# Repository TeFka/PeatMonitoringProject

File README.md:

# University group project
# Peat monitoring device
### This is the repository for used for storage of all relevant resources used for the university group project.<br>
### The project involved development of a device that would be placed in a peat and provides measuremetns about the peat state.</br>
### Measurements include:
* Surface elevation - shows how much peat surface changed water in it.</br>
* Water pressure - shows the pressure created by the peat water table.</br>
* Temperature - shows temperature of surroundings around the device.</br>
* Operate for at least 6 months unsupervised and store all data.</br>
### A poster was created for the device:</br>
</br>
### The respository was created and managed by Danielius Zurlys. Project work done by Danielius Zurlys:<br>
* All embedded software<br>
* Hardware and mechanical designs for pressure sensor<br>
* Hardware and mechanical designs for temperature sensor<br>
### Work done by other group members:<br>
* Oliver Davies - Developed PCB for STM32<br>
* Chuan Loo - Developed PCB for battery control<br>
* Sever Dragomir - Design for main case and elevantion sensor.<br>
* James Bodenham - RF communication hardware choice and logic<br>

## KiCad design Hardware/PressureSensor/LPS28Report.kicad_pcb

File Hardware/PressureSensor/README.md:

# Pressure sensor PCB
Developed PCB to host pressure sensor. The used pressure sensor is LPS28DFW (.pdf datasheet file provded).
The sensor is very small and the PCB is meant to enable connection between sensor and standart connections.

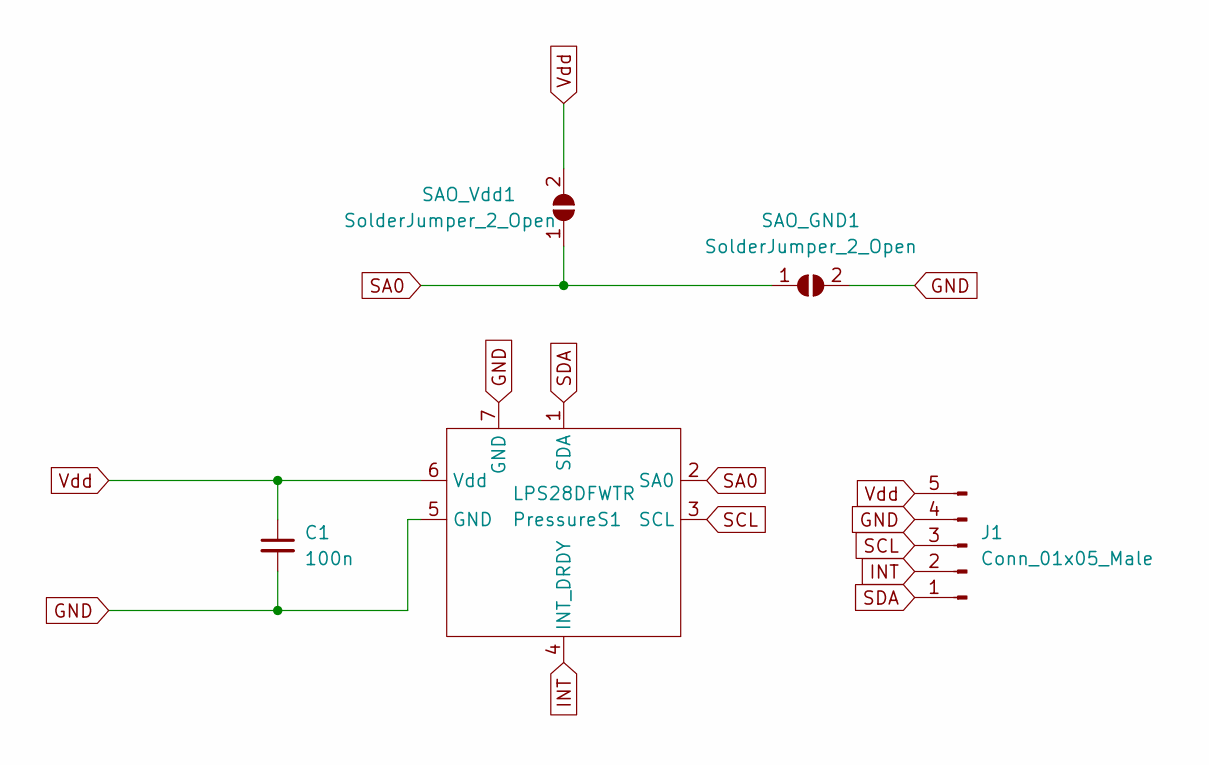
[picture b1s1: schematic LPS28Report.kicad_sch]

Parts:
C1: 100n; C_0603_1608Metric_Pad1.08x0.95mm_HandSolder
J1: Conn_01x05_Male; PinHeader_1x05_P1.00mm_Vertical_SMD_Pin1Left
PressureS1: LPS28DFWTR
SAO_GND1: SolderJumper_2_Open; SolderJumper-2_P1.3mm_Open_Pad1.0x1.5mm
SAO_Vdd1: SolderJumper_2_Open; SolderJumper-2_P1.3mm_Open_Pad1.0x1.5mm

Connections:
GND: C1.2, J1.4, PressureS1.5 (GND), PressureS1.7 (GND), SAO_GND1.2 (B)
INT: J1.2, PressureS1.4 (INT_DRDY)
SA0: PressureS1.2 (SA0), SAO_GND1.1 (A), SAO_Vdd1.1 (A)
SCL: J1.3, PressureS1.3 (SCL)
SDA: J1.1, PressureS1.1 (SDA)
Vdd: C1.1, J1.5, PressureS1.6 (Vdd), SAO_Vdd1.2 (B)

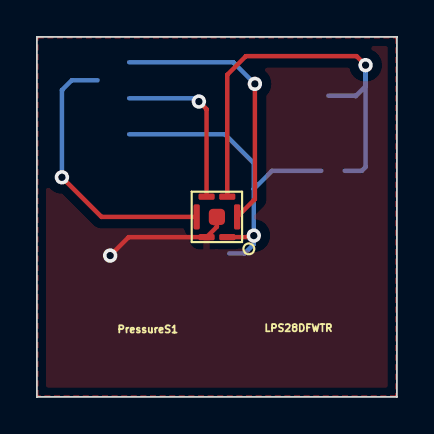
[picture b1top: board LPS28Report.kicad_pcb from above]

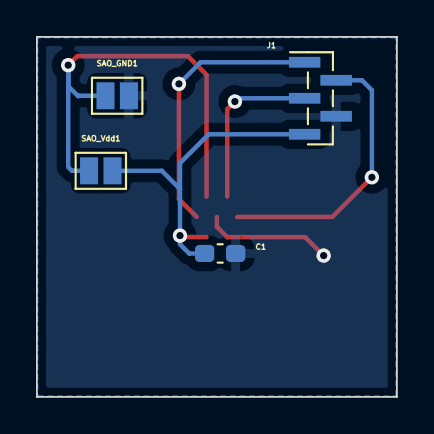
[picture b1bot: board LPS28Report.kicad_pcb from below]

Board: 2 copper layers, 20.0 x 20.0 mm, 5 parts (4 on the bottom side), 6 nets.

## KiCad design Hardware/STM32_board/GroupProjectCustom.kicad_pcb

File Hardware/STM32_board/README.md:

# STM32 chip PCB</br>
Designed by Oliver Davies</br>
The main PCB for STM32 chip. Provides SPI, I2C, UART and analogue connections that allow communicaton with all relevant components. Connection to the battery is also availalbe to provide power.</br>

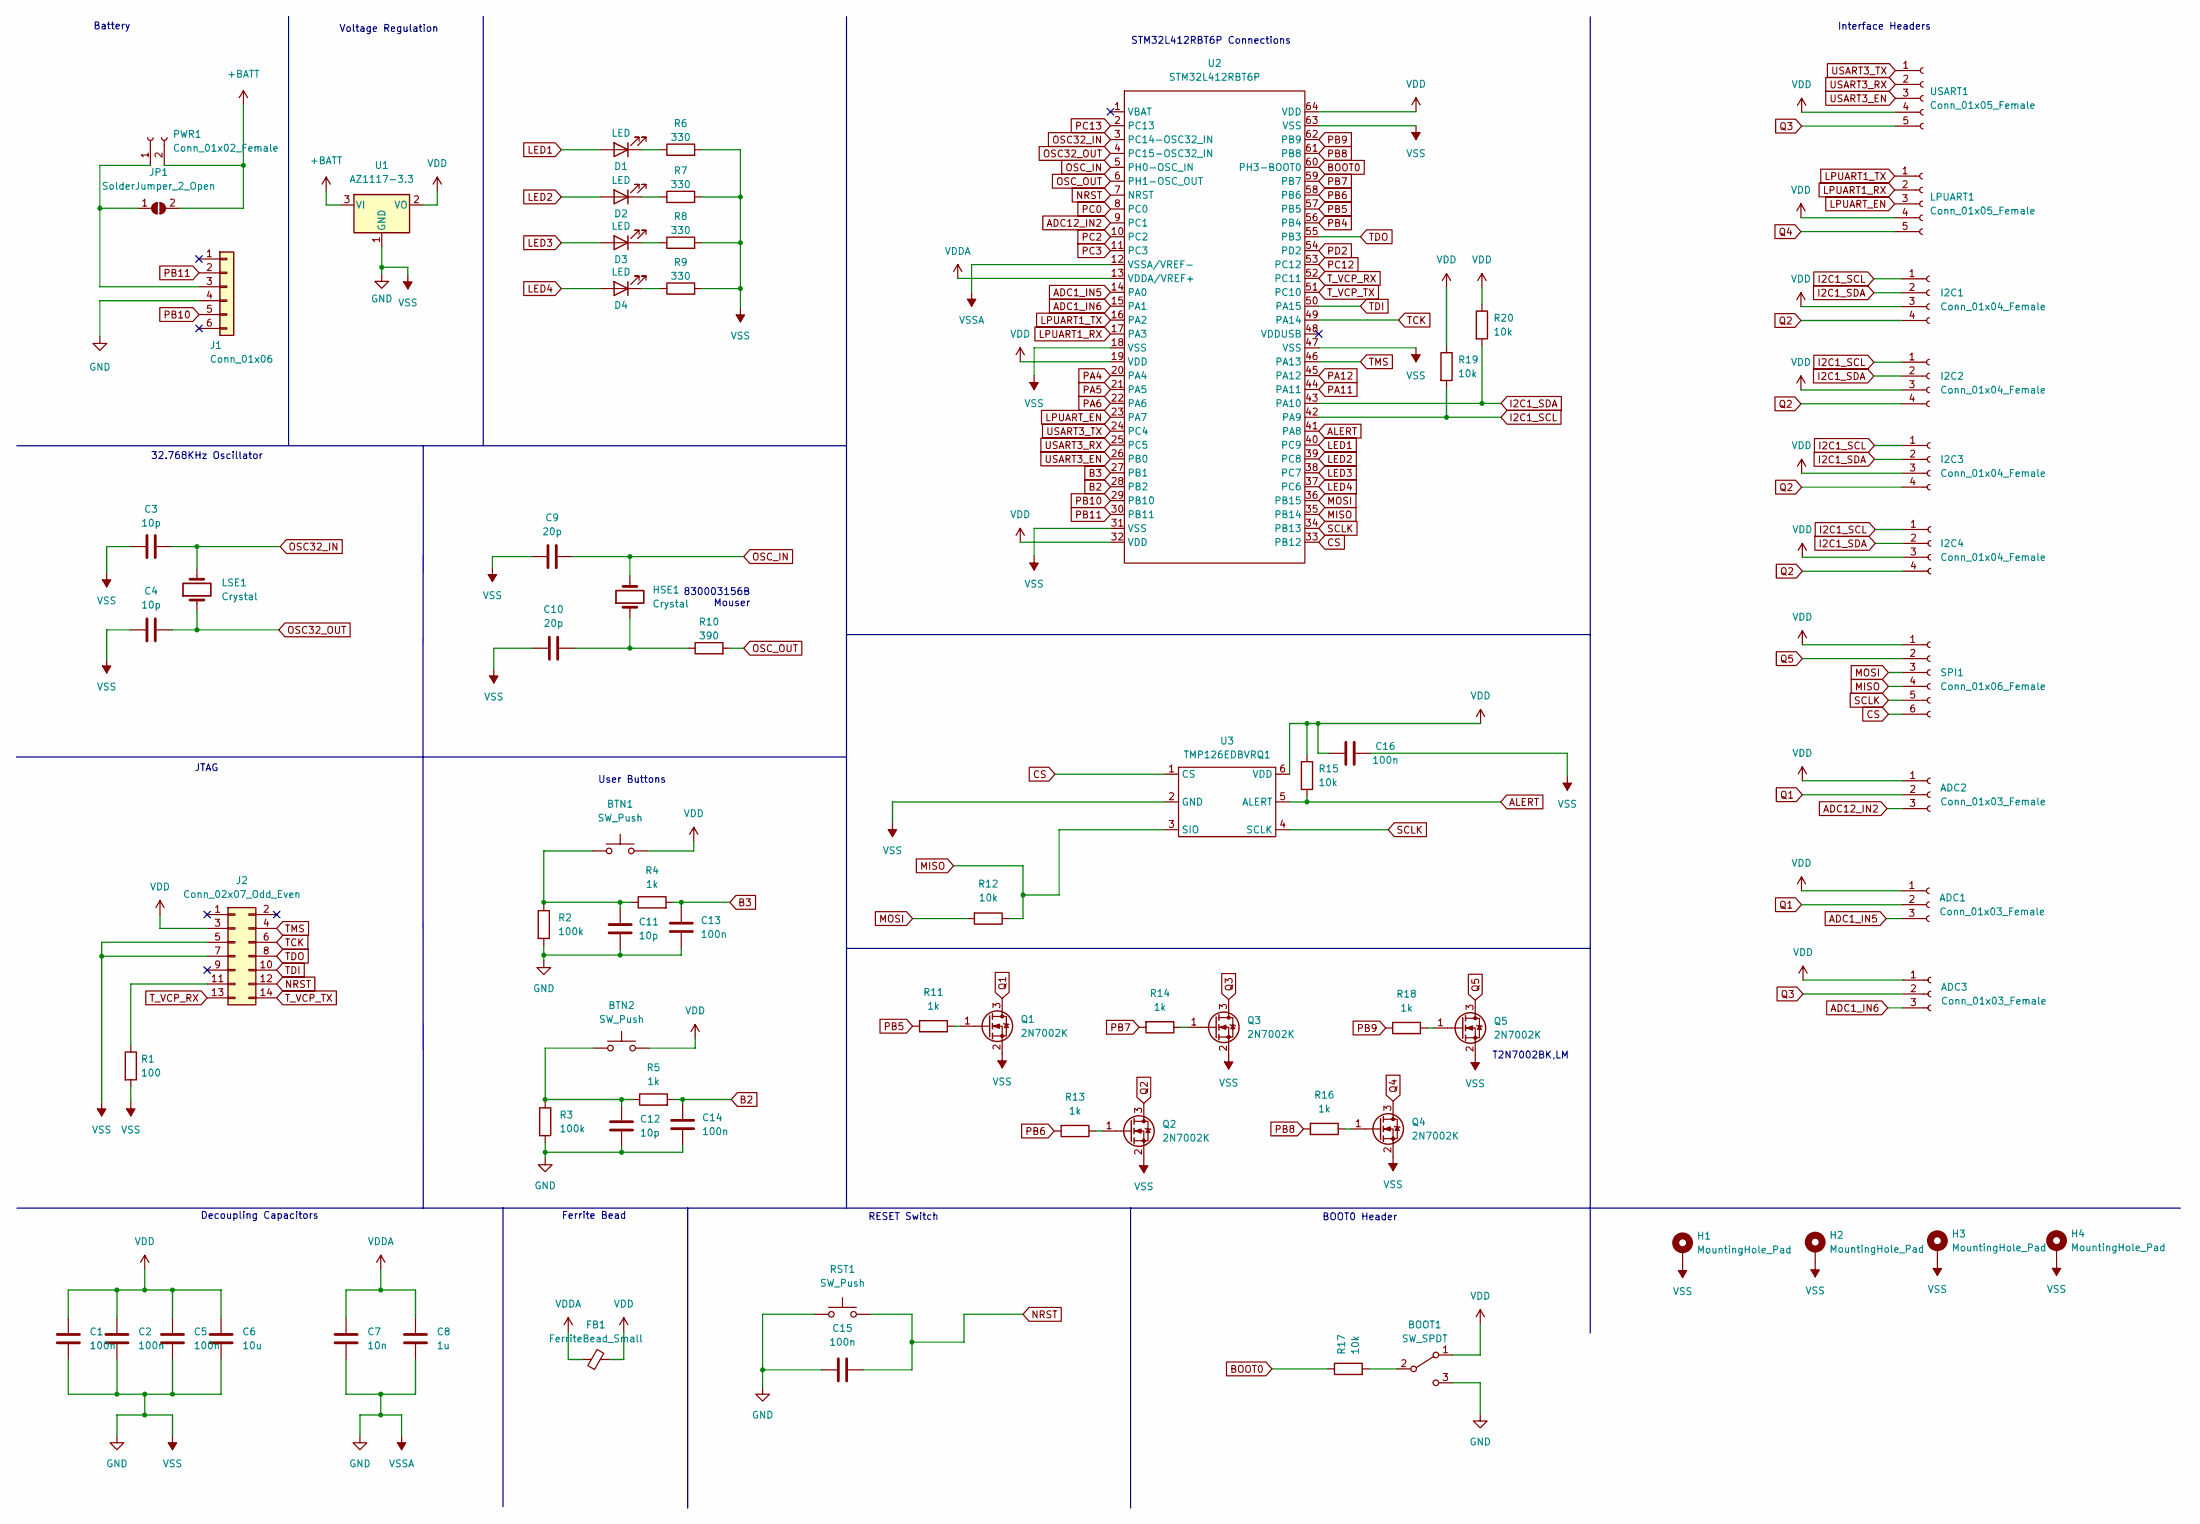
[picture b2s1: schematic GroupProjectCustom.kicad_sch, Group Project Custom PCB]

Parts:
ADC1, ADC2, ADC3: Conn_01x03_Female; PinHeader_1x03_P2.54mm_Vertical
BOOT1: SW_SPDT; PinHeader_1x03_P2.54mm_Vertical
BTN1, BTN2: SW_Push; SW_Push_1P1T_NO_Vertical_Wuerth_434133025816
C1, C2, C5, C13, C14, C15, C16: 100n; C_0603_1608Metric_Pad1.08x0.95mm_HandSolder
C3, C4, C11, C12: 10p; C_0603_1608Metric_Pad1.08x0.95mm_HandSolder
C6: 10u; C_0603_1608Metric_Pad1.08x0.95mm_HandSolder
C7: 10n; C_0603_1608Metric_Pad1.08x0.95mm_HandSolder
C8: 1u; C_0603_1608Metric_Pad1.08x0.95mm_HandSolder
C9, C10: 20p; C_0603_1608Metric_Pad1.08x0.95mm_HandSolder
D1, D2, D3, D4: LED; LED_0603_1608Metric_Pad1.05x0.95mm_HandSolder
FB1: FerriteBead_Small; R_0603_1608Metric_Pad0.98x0.95mm_HandSolder
H1, H2, H3, H4: MountingHole_Pad; MountingHole_2.2mm_M2_Pad_Via
HSE1: Crystal; Crystal_HC49-4H_Vertical
I2C1, I2C2, I2C3, I2C4: Conn_01x04_Female; PinHeader_1x04_P2.54mm_Vertical
J1: Conn_01x06; PinHeader_1x06_P2.54mm_Vertical
J2: Conn_02x07_Odd_Even; PinHeader_2x07_P1.27mm_Vertical_SMD
JP1: SolderJumper_2_Open; SolderJumper-2_P1.3mm_Open_TrianglePad1.0x1.5mm
LPUART1: Conn_01x05_Female; PinHeader_1x05_P2.54mm_Vertical
LSE1: Crystal; Crystal_SMD_MicroCrystal_CC7V-T1A-2Pin_3.2x1.5mm_HandSolder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
PWR1: Conn_01x02_Female; PinHeader_1x02_P2.54mm_Vertical
Q1, Q2, Q3, Q4, Q5: 2N7002K; SOT-23
R1: 100; R_0603_1608Metric
R2, R3: 100k; R_0603_1608Metric
R4, R5, R11, R13, R14, R16, R18: 1k; R_0603_1608Metric
R6, R7, R8, R9: 330; R_0603_1608Metric
R10: 390; R_0603_1608Metric
R12, R15, R17, R19, R20: 10k; R_0603_1608Metric
RST1: SW_Push; SW_Push_1P1T_NO_Vertical_Wuerth_434133025816
SPI1: Conn_01x06_Female; PinHeader_1x06_P2.54mm_Vertical
U1: AZ1117-3.3; SOT-223-3_TabPin2
U2: STM32L412RBT6P; STM32L412RBT6P_Foot
U3: TMP126EDBVRQ1; SOT-23-6_Handsoldering
USART1: Conn_01x05_Female; PinHeader_1x05_P2.54mm_Vertical

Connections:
+BATT: JP1.2 (B), PWR1.2, U1.3 (VI)
ADC1_IN5: ADC1.3, U2.14 (PA0)
ADC1_IN6: ADC3.3, U2.15 (PA1)
ADC12_IN2: ADC2.3, U2.9 (PC1)
ALERT: R15.2, U2.41 (PA8), U3.5 (ALERT)
B2: C14.1, R5.2, U2.28 (PB2)
B3: C13.1, R4.2, U2.27 (PB1)
BOOT0: R17.1, U2.60 (PH3-BOOT0)
CS: SPI1.6, U2.33 (PB12), U3.1 (CS)
GND: BOOT1.3 (C), C1.2, C2.2, C3.1, C4.1, C5.2, C6.2, C7.2, C8.2, C9.1, C10.1, C11.1, C12.1, C13.2, C14.2, C15.1, C16.2, H1.1, H2.1, H3.1, H4.1, J1.4, J2.5, J2.7, Q1.2 (S), Q2.2 (S), Q3.2 (S), Q4.2 (S), Q5.2 (S), R1.2, R2.2, R3.2, R6.2, R7.2, R8.2, R9.2, RST1.1, U1.1 (GND), U2.12 (VSSA/VREF-), U2.18 (VSS), U2.31 (VSS), U2.47 (VSS), U2.63 (VSS), U3.2 (GND)
I2C1_SCL: I2C1.1, I2C2.1, I2C3.1, I2C4.1, R19.2, U2.42 (PA9)
I2C1_SDA: I2C1.2, I2C2.2, I2C3.2, I2C4.2, R20.2, U2.43 (PA10)
LED1: D1.2 (A), U2.40 (PC9)
LED2: D2.2 (A), U2.39 (PC8)
LED3: D3.2 (A), U2.38 (PC7)
LED4: D4.2 (A), U2.37 (PC6)
LPUART1_RX: LPUART1.2, U2.17 (PA3)
LPUART1_TX: LPUART1.1, U2.16 (PA2)
LPUART_EN: LPUART1.3, U2.23 (PA7)
MISO: R12.1, SPI1.4, U2.35 (PB14), U3.3 (SIO)
MOSI: R12.2, SPI1.3, U2.36 (PB15)
NRST: C15.2, J2.12, RST1.2, U2.7 (NRST)
unnamed: BOOT1.2 (B), R17.2
unnamed: BTN1.1, C11.2, R2.1, R4.1
unnamed: BTN2.1, C12.2, R3.1, R5.1
unnamed: C10.2, HSE1.1, R10.1
unnamed: D1.1 (K), R6.1
unnamed: D2.1 (K), R7.1
unnamed: D3.1 (K), R8.1
unnamed: D4.1 (K), R9.1
unnamed: J1.3, JP1.1 (A), PWR1.1
unnamed: J2.11, R1.1
unnamed: Q1.1 (G), R11.1
unnamed: Q2.1 (G), R13.1
unnamed: Q3.1 (G), R14.1
unnamed: Q4.1 (G), R16.1
unnamed: Q5.1 (G), R18.1
OSC32_IN: C3.2, LSE1.2, U2.3 (PC14-OSC32_IN)
OSC32_OUT: C4.2, LSE1.1, U2.4 (PC15-OSC32_IN)
OSC_IN: C9.2, HSE1.2, U2.5 (PH0-OSC_IN)
OSC_OUT: R10.2, U2.6 (PH1-OSC_OUT)
PA4: U2.20 (PA4)
PA5: U2.21 (PA5)
PA6: U2.22 (PA6)
PA11: U2.44 (PA11)
PA12: U2.45 (PA12)
PB4: U2.56 (PB4)
PB5: R11.2, U2.57 (PB5)
PB6: R13.2, U2.58 (PB6)
PB7: R14.2, U2.59 (PB7)
PB8: R16.2, U2.61 (PB8)
PB9: R18.2, U2.62 (PB9)
PB10: J1.5, U2.29 (PB10)
PB11: J1.2, U2.30 (PB11)
PC0: U2.8 (PC0)
PC2: U2.10 (PC2)
PC3: U2.11 (PC3)
PC12: U2.53 (PC12)
PC13: U2.2 (PC13)
PD2: U2.54 (PD2)
Q1: ADC1.2, ADC2.2, Q1.3 (D)
Q2: I2C1.4, I2C2.4, I2C3.4, I2C4.4, Q2.3 (D)
Q3: ADC3.2, Q3.3 (D), USART1.5
Q4: LPUART1.5, Q4.3 (D)
Q5: Q5.3 (D), SPI1.2
SCLK: SPI1.5, U2.34 (PB13), U3.4 (SCLK)
TCK: J2.6, U2.49 (PA14)
TDI: J2.10, U2.50 (PA15)
TDO: J2.8, U2.55 (PB3)
TMS: J2.4, U2.46 (PA13)
T_VCP_RX: J2.13, U2.52 (PC11)
T_VCP_TX: J2.14, U2.51 (PC10)
USART3_EN: U2.26 (PB0), USART1.3
USART3_RX: U2.25 (PC5), USART1.2
USART3_TX: U2.24 (PC4), USART1.1
VDD: ADC1.1, ADC2.1, ADC3.1, BOOT1.1 (A), BTN1.2, BTN2.2, C1.1, C2.1, C5.1, C6.1, C16.1, FB1.2, I2C1.3, I2C2.3, I2C3.3, I2C4.3, J2.3, LPUART1.4, R15.1, R19.1, R20.1, SPI1.1, U1.2 (VO), U2.19 (VDD), U2.32 (VDD), U2.64 (VDD), U3.6 (VDD), USART1.4
VDDA: C7.1, C8.1, FB1.1, U2.13 (VDDA/VREF+)

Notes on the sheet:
RESET Switch
JTAG
BOOT0 Header
Ferrite Bead
User Buttons
STM32L412RBT6P Connections
Interface Headers
Decoupling Capacitors
Voltage Regulation
Battery
32.768KHz Oscillator
830003156B Mouser
T2N7002BK,LM

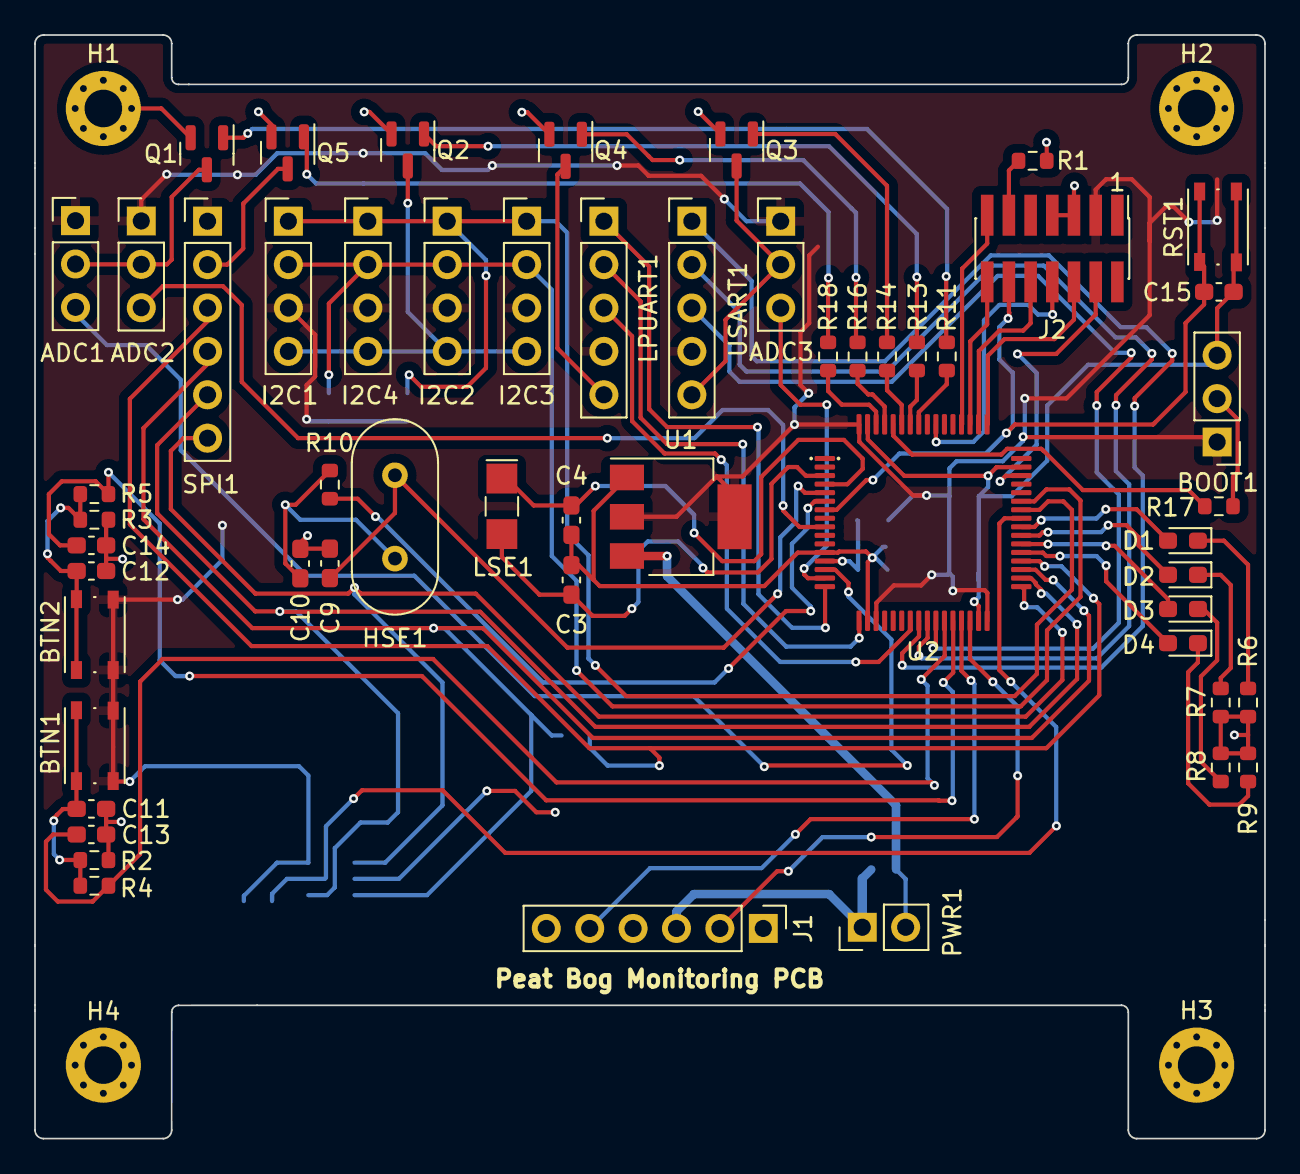
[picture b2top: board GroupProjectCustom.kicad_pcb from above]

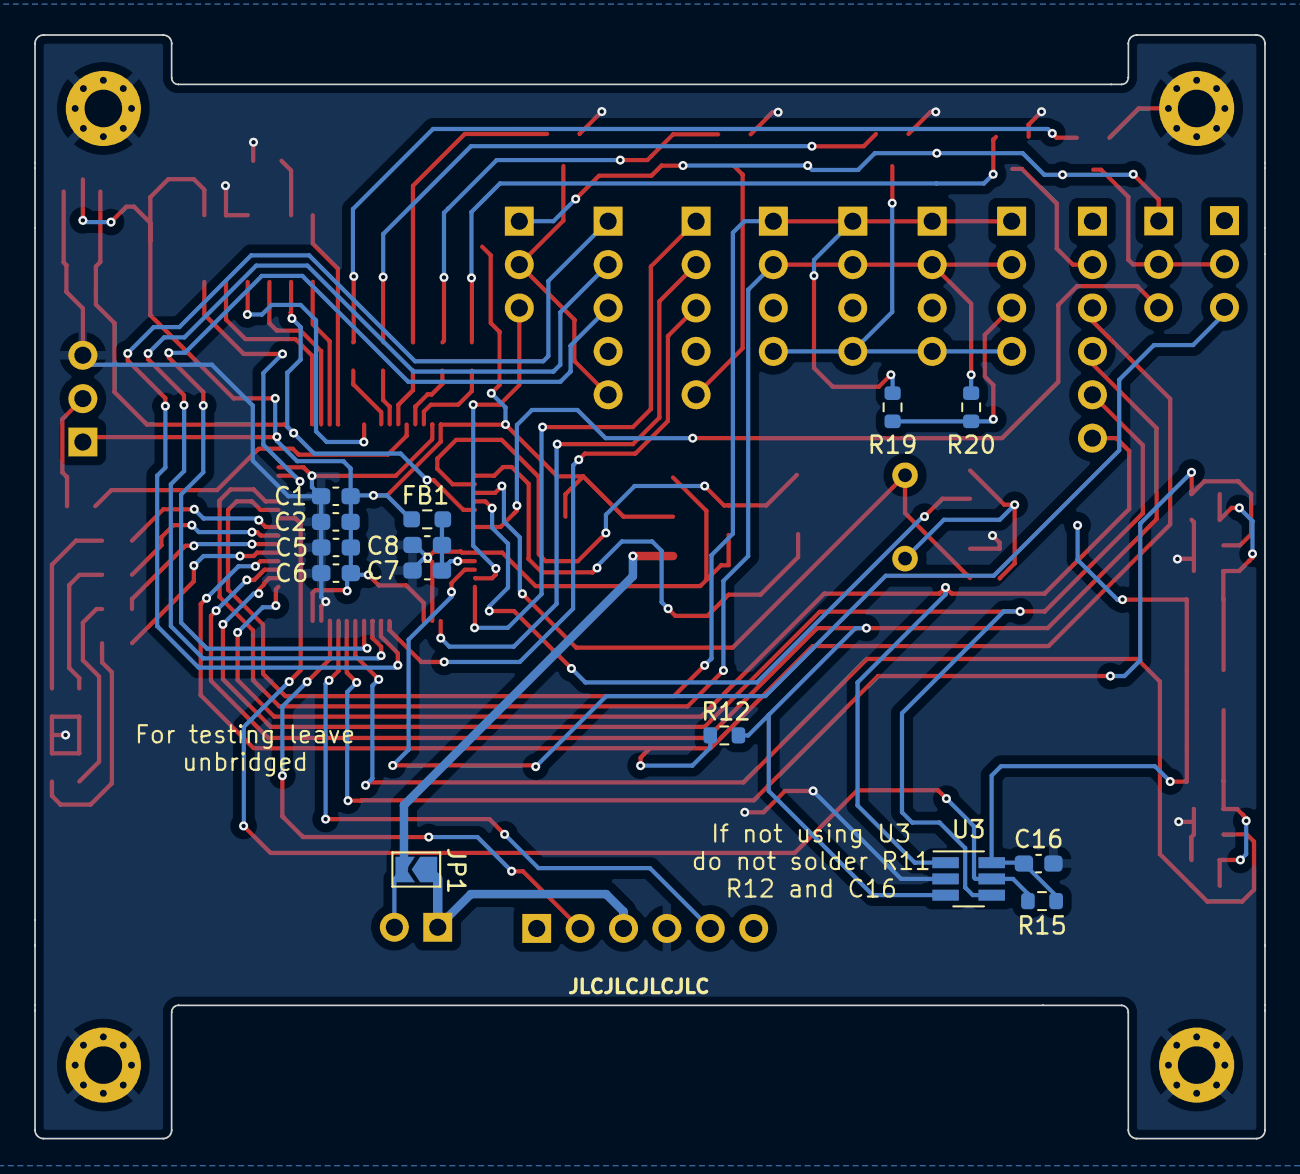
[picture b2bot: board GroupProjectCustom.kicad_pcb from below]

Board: 2 copper layers, 72.0 x 64.6 mm, 73 parts (14 on the bottom side), 65 nets.

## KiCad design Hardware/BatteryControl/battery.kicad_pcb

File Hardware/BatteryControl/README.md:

# Battery management PCB PCB</br>
### Designed by Chuan Loo</br>
### The PCB is meant to allow efficient and safew usage of batteries. Main functions are:</br>
* Reduce battery voltage to safe levels for the PCB.</br
* Use one battery at a time even if two are connected, when one battery is depleted, only then the PCB starts retrieving power from second battery.</br

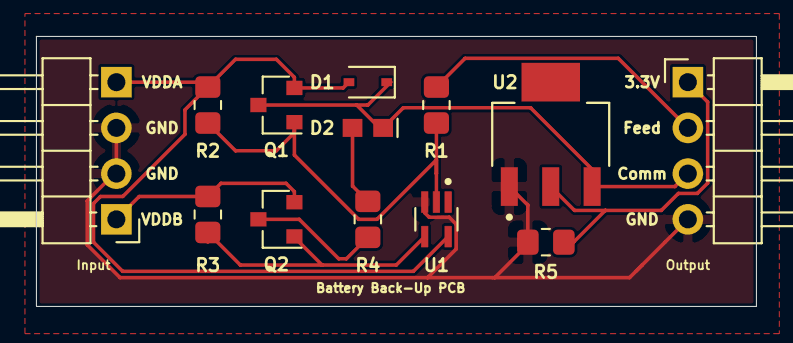
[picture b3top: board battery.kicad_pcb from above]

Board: 2 copper layers, 40.0 x 15.0 mm, 13 parts (0 on the bottom side), 10 nets.

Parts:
D1: 1N4148WS; D_SOD-323
D2: RED; 0603_DIODE
Input: Conn_01x04_Male; PinHeader_1x04_P2.54mm_Horizontal
Output: Conn_01x04_Male; PinHeader_1x04_P2.54mm_Horizontal
Q1, Q2: IRLML6402; SOT-23
R1: 825; R_0805_2012Metric_Pad1.20x1.40mm_HandSolder
R2, R3, R5: 10k; R_0805_2012Metric_Pad1.20x1.40mm_HandSolder
R4: 200; R_0805_2012Metric_Pad1.20x1.40mm_HandSolder
U1: 74AHC1G04; SOT65P210X110-5N
U2: LM1117-3.3; VREG_LM1117MP-3.3_NOPB

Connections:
3.3V: Output.1, R5.1, U2.2
Comm: D1.1, D2.1, Output.3, Q1.3, U2.3
Feed: Output.2, R1.2
GND: Input.2, Input.3, Output.4, R5.2, U1.3, U2.1
unnamed: D2.2, R4.1
unnamed: Q1.1, R1.1, R2.2, U1.2
unnamed: Q2.1, R3.1, U1.4
unnamed: Q2.3, R4.2
VDDA: D1.2, Input.4, Q1.2, R2.1, U1.5
VDDB: Input.1, Q2.2, R3.2

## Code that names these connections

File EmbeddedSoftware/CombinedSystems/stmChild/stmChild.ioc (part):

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Mcu.Name=STM32L412RBTxP
Mcu.Package=LQFP64
Mcu.UserName=STM32L412RBTxP
PA0.Signal=ADCx_IN5
PA1.Signal=ADCx_IN6
PA10.Mode=I2C
PA10.Signal=I2C1_SDA
PA13\ (JTMS/SWDIO).Mode=Serial_Wire
PA13\ (JTMS/SWDIO).Signal=SYS_JTMS-SWDIO
PA14\ (JTCK/SWCLK).Mode=Serial_Wire
PA14\ (JTCK/SWCLK).Signal=SYS_JTCK-SWCLK
PA2.Mode=Asynchronous
PA2.Signal=LPUART1_TX
PA3.Mode=Asynchronous
PA3.Signal=LPUART1_RX
PA7.Signal=GPIO_Output
PA9.Mode=I2C
PA9.Signal=I2C1_SCL
PB0.Signal=GPIO_Output
PB1.Signal=GPIO_Input
PB11.Mode=Asynchronous
PB11.Signal=USART3_RX
PB12.Signal=GPIO_Output
PB13.Mode=Full_Duplex_Master
PB13.Signal=SPI2_SCK
PB14.Mode=Full_Duplex_Master
PB14.Signal=SPI2_MISO
PB15.Mode=Full_Duplex_Master
PB15.Signal=SPI2_MOSI
PB2.Signal=GPIO_Input
PB5.Signal=GPIO_Output
PB6.Signal=GPIO_Output
PB7.Signal=GPIO_Output
PB8.Signal=GPIO_Output
PB9.Signal=GPIO_Output
PC1.Signal=ADCx_IN2
PC14-OSC32_IN\ (PC14).Mode=LSE-External-Oscillator
PC14-OSC32_IN\ (PC14).Signal=RCC_OSC32_IN
PC15-OSC32_OUT\ (PC15).Mode=LSE-External-Oscillator
PC15-OSC32_OUT\ (PC15).Signal=RCC_OSC32_OUT
PC4.Mode=Asynchronous
PC4.Signal=USART3_TX
PC6.Signal=GPIO_Output
PC7.Signal=GPIO_Output
PC8.Signal=GPIO_Output
PC9.Signal=GPIO_Output
PH0-OSC_IN\ (PH0).Mode=HSE-External-Oscillator
PH0-OSC_IN\ (PH0).Signal=RCC_OSC_IN
PH1-OSC_OUT\ (PH1).Mode=HSE-External-Oscillator
PH1-OSC_OUT\ (PH1).Signal=RCC_OSC_OUT
RCC.HSE_VALUE=8000000
RCC.SYSCLKFreq_VALUE=16000000
RCC.SYSCLKSource=RCC_SYSCLKSOURCE_HSI
board=custom

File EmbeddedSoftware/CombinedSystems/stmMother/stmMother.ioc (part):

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Mcu.Name=STM32L412RBTxP
Mcu.Package=LQFP64
Mcu.UserName=STM32L412RBTxP
PA1.Signal=ADCx_IN6
PA10.Signal=GPIO_Output
PA2.Mode=Asynchronous
PA2.Signal=LPUART1_TX
PA3.Mode=Asynchronous
PA3.Signal=LPUART1_RX
PB10.Signal=GPIO_Input
PB12.Signal=GPIO_Output
PB13.Mode=Full_Duplex_Master
PB13.Signal=SPI2_SCK
PB14.Mode=Full_Duplex_Master
PB14.Signal=SPI2_MISO
PB15.Mode=Full_Duplex_Master
PB15.Signal=SPI2_MOSI
PB2.Signal=GPIO_Input
PB6.Signal=GPIO_Output
PB7.Signal=GPIO_Output
PB8.Signal=GPIO_Output
PB9.Signal=GPIO_Output
PC11.Mode=Asynchronous
PC11.Signal=USART3_RX
PC13.Mode=Calibration_512Hz
PC13.Signal=RTC_OUT_CALIB
PC14-OSC32_IN\ (PC14).Mode=LSE-External-Oscillator
PC14-OSC32_IN\ (PC14).Signal=RCC_OSC32_IN
PC15-OSC32_OUT\ (PC15).Mode=LSE-External-Oscillator
PC15-OSC32_OUT\ (PC15).Signal=RCC_OSC32_OUT
PC4.Mode=Asynchronous
PC4.Signal=USART3_TX
PC6.Signal=GPIO_Output
PC7.Signal=GPIO_Output
PC8.Signal=GPIO_Output
PC9.Signal=GPIO_Output
PH0-OSC_IN\ (PH0).Mode=HSE-External-Oscillator
PH0-OSC_IN\ (PH0).Signal=RCC_OSC_IN
PH1-OSC_OUT\ (PH1).Mode=HSE-External-Oscillator
PH1-OSC_OUT\ (PH1).Signal=RCC_OSC_OUT
RCC.HSE_VALUE=8000000
RCC.SYSCLKFreq_VALUE=16000000
RCC.SYSCLKSource=RCC_SYSCLKSOURCE_HSI
board=custom

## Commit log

2023-04-29 Main code upload
2023-05-11 Final code
2023-05-11 Final change to depth measurement code
2023-10-02 Changes to ReadMe file
2024-09-02 Added documentation 1
2024-09-02 Added documentation 2
2024-09-02 Added documentation 3
2024-09-02 Added documentation 4
2024-09-02 Added documentation 5
2024-09-02 Added documentation 6
2024-09-02 Added documentation 7
